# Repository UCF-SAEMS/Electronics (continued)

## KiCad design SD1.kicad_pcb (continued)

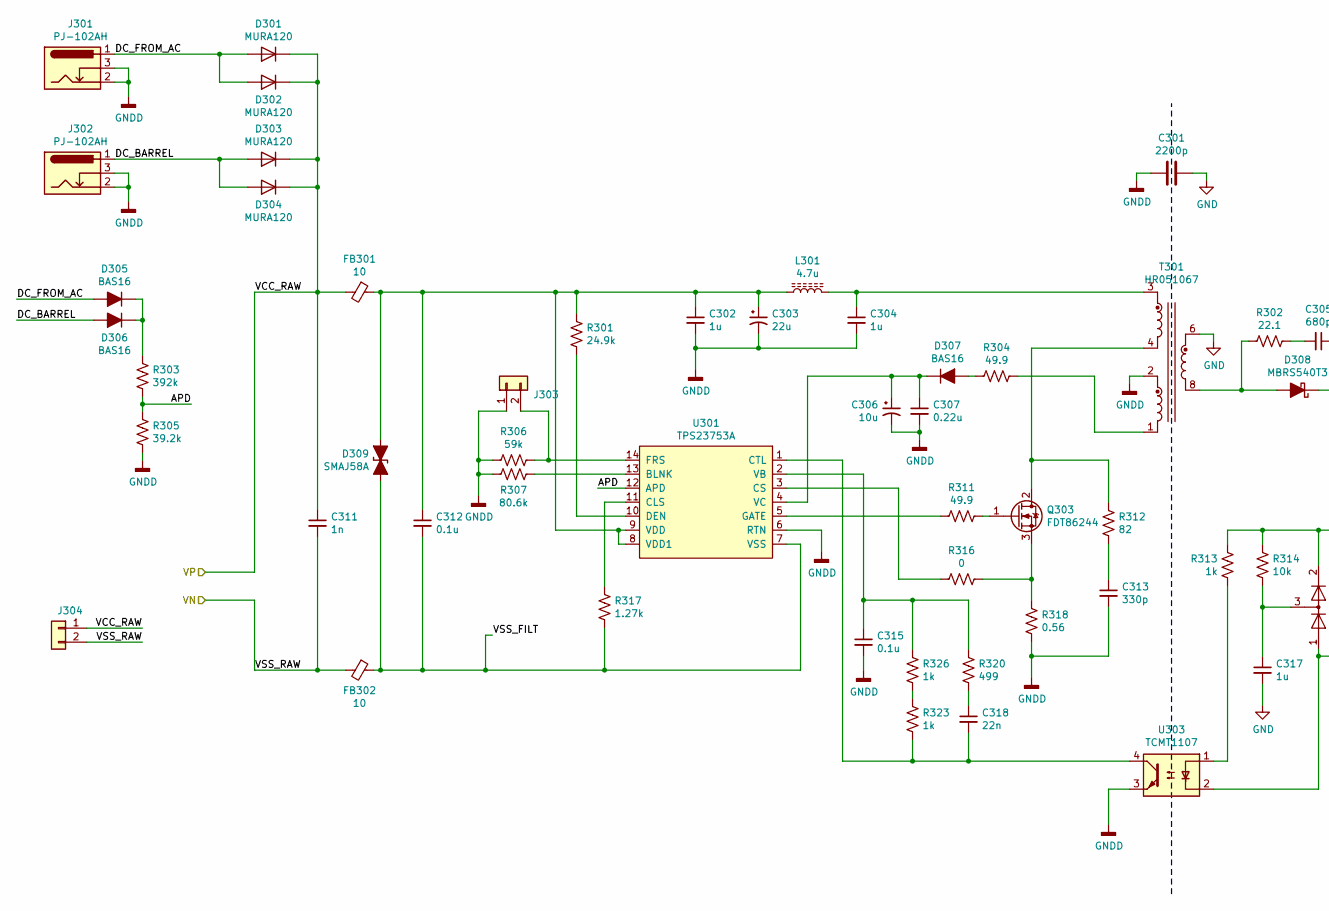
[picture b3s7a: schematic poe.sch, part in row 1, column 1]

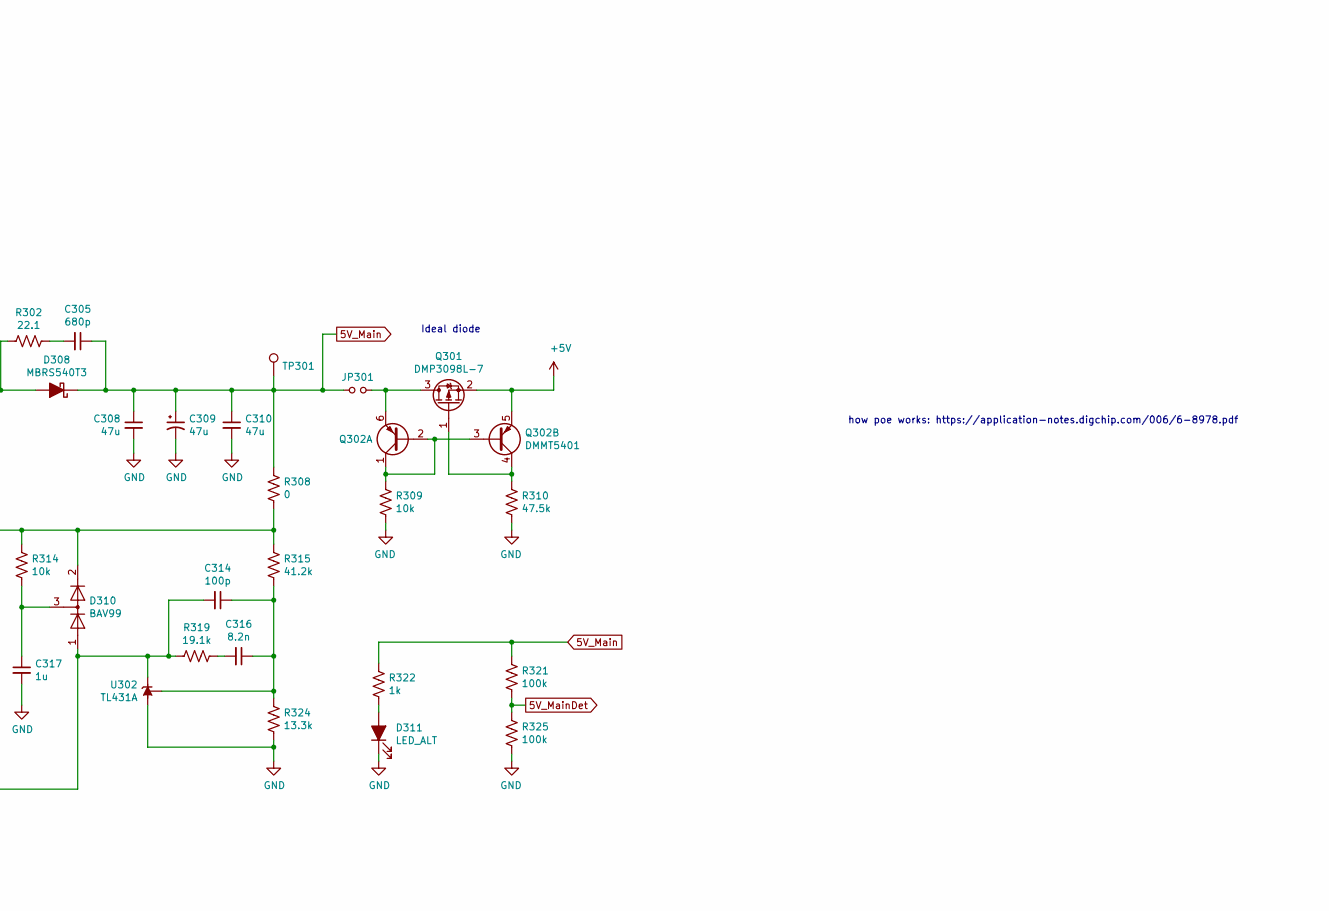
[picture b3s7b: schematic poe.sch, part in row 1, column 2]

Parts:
C301: 2200p; C_1812_4532Metric; Voltage 2kV; MPN 202S43W222KV4E; LCSC C426624
C302, C304: 1u; C_1210_3225Metric; Voltage 100V; MPN C1210C105K1RACAUTO; Digikey 399-7044-1-ND
C303: 22u; C_Elec_6.3x7.7; Voltage 63V; MPN EEHZC1J220XP; Digikey P15467CT-ND
C305: 680p; C_0603_1608Metric; Voltage 25V; MPN 0603B681K500CT; Digikey 1292-1458-1-ND
C306: 10u; CP_Elec_4x5.8; Voltage 16V; MPN EEEHD1C100AR; Digikey PCE4949CT-ND
C307: 0.22u; C_0805_2012Metric; Voltage 25V; MPN CL21B224KBFNNNE; Digikey 1276-1093-1-ND
C308, C310: 47u; C_1210_3225Metric; Voltage 10V; MPN 1210X476K160CT; LCSC C396815
C309: 47u; CP_Elec_4x5.8; Voltage 6.3V; MPN EEEFT1C470AR; Digikey P15090CT-ND
C311: 1n; C_0805_2012Metric; Voltage 100V; MPN CL21B102KCANNNC; Digikey 1276-1169-1-ND
C312: 0.1u; C_0805_2012Metric; Voltage 100V; MPN CL21B104KCFWPNE; Digikey 1276-6733-1-ND
C313: 330p; C_0805_2012Metric; Voltage 200V; MPN CC0805KRX7RABB331; Digikey 311-4334-1-ND
C314: 100p; C_0603_1608Metric; Voltage 50V; MPN CL10C101JC8NNNC; Digikey 1276-1295-1-ND
C315: 0.1u; C_0603_1608Metric; Voltage 50V; MPN 0603B104K500CT; Digikey 1292-1643-1-ND
C316: 8.2n; C_0603_1608Metric; Voltage 50V; MPN CC0603KRX7R9BB822; Digikey 311-1811-1-ND
C317: 1u; C_0603_1608Metric; MPN TMK107B7105KA-T; Digikey 587-2984-1-ND
C318: 22n; C_0603_1608Metric; Voltage 50V; MPN CL10B223KC8WPNC; Digikey 1276-CL10B223KC8WPNCCT-ND
D301, D302, D303, D304: MURA120; D_SMA; MPN MURA120T3G; Digikey MURA120T3GOSCT-ND
D305, D306, D307: BAS16; D_SOT-23_ANK; MPN BAS16-7-F; Digikey BAS16-FDICT-ND
D308: MBRS540T3; D_SMC; MPN MBRS540T3G; LCSC C31849
D309: SMAJ58A; D_SMA; MPN SMAJ58CA-E3/61; Digikey SMAJ58CA-E3/61GICT-ND
D310: BAV99; SOT-23; MPN BAV99,215; Digikey 1727-2914-1-ND
D311: LED_ALT; LED_0603_1608Metric; MPN 150060RS75000; Digikey 732-4978-1-ND
FB301, FB302: 10; L_0603_1608Metric; MPN PBY160808T-110Y-N; LCSC C280672
J301, J302: PJ-102AH; BarrelJack_CUI_PJ-102AH_Horizontal; MPN PJ-102AH; Digikey CP-102AH-ND
J303, J304: Conn_01x02; PinSocket_1x02_P2.54mm_Vertical
JP301: Jumper_NO_Small; SolderJumper-2_P1.3mm_Open_TrianglePad1.0x1.5mm
L301: 4.7u; L_Taiyo-Yuden_MD-4040; MPN SLW4030S4R7MST; Digikey 587-5994-1-ND
Q301: DMP3098L-7; SOT-23-6; MPN DMP3098L-7; Digikey DMP3098LDICT-ND
Q302: DMMT5401; SOT-23-6; MPN DMMT5401-7-F; Digikey DMMT5401-FDICT-ND
Q303: FDT86244; SOT-223-3_TabPin2; MPN FDT86244; LCSC C489347
R301: 24.9k; R_0603_1608Metric; MPN RC0603FR-0724K9L; Digikey 311-24.9KHRCT-ND
R302: 22.1; R_0603_1608Metric; MPN RC0603FR-0722R1L; Digikey 311-22.1HRCT-ND
R303: 392k; R_0603_1608Metric; MPN RC0603FR-07392KL; Digikey 311-392KHRCT-ND
R304, R311: 49.9; R_0603_1608Metric; MPN RC0603FR-0749R9L; Digikey 311-49.9HRCT-ND
R305: 39.2k; R_0603_1608Metric; MPN AC0603FR-0739K2L; Digikey YAG3602CT-ND
R306: 59k; R_0603_1608Metric; MPN RC0603FR-0759KL; Digikey 311-59.0KHRCT-ND
R307: 80.6k; R_0603_1608Metric; MPN RC0603FR-0780K6L; Digikey 311-80.6KHRCT-ND
R308, R316: 0; R_0603_1608Metric
R309, R314: 10k; R_0603_1608Metric; MPN RC0603FR-0710KL; Digikey 311-10.0KHRCT-ND
R310: 47.5k; R_0603_1608Metric; MPN RC0603FR-0747K5L; Digikey 311-47.5KHRCT-ND
R312: 82; R_2010_5025Metric; LCSC C421678, C20464
R313, R322, R323, R326: 1k; R_0603_1608Metric; MPN RC0603FR-071KL; Digikey 311-1.00KHRCT-ND
R315: 41.2k; R_0603_1608Metric; MPN RC0603FR-0741K2L; Digikey 311-41.2KHRCT-ND
R317: 1.27k; R_0603_1608Metric; MPN RC0603FR-071K27L; Digikey 311-1.27KHRCT-ND
R318: 0.56; R_1206_3216Metric; MPN KDV12FR560ET; Digikey 273-KDV12FR560ETCT-ND
R319: 19.1k; R_0603_1608Metric; MPN AC0603FR-0719K1L; Digikey 13-AC0603FR-0719K1LCT-ND
R320: 499; R_0603_1608Metric; MPN AC0603FR-07499RL; Digikey 13-AC0603FR-07499RLCT-ND
R321, R325: 100k; R_0603_1608Metric; MPN RC0603FR-07100KL; Digikey 311-100KHRCT-ND
R324: 13.3k; R_0603_1608Metric; MPN RC0603FR-0713K3L; Digikey 311-13.3KHRCT-ND
T301: HR051067; MPN HR051067; LCSC C93830
TP301: TestPoint; PinSocket_1x01_P2.54mm_Vertical
U301: TPS23753A; TSSOP-14_4.4x5mm_P0.65mm; MPN TPS23753APWR; Digikey 296-39365-1-ND
U302: TL431A; SOT-23; MPN TL431ACDBZR; Digikey 296-17328-1-ND
U303: TCMT1107; SOIC-4_4.55x2.6mm_P1.27mm; MPN TCMT1107; LCSC C81148

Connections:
5V_Main: C305.1, C308.1, C309.1, C310.1, D308.1 (K), JP301.1, R308.2, R321.2, R322.1, TP301.1; also elsewhere on the board
5V_MainDet: R321.1, R325.2; also elsewhere on the board
+5V: Q301.2 (S), Q302.5 (E2); also elsewhere on the board
/Eth + PoE/PoE Flyback/APD: R303.2, R305.1, U301.12 (APD)
/Eth + PoE/PoE Flyback/DC_BARREL: D303.2 (A), D304.2 (A), D306.2 (A), J302.1
/Eth + PoE/PoE Flyback/DC_FROM_AC: D301.2 (A), D302.2 (A), D305.2 (A), J301.1
/Eth + PoE/PoE Flyback/VN: C311.2, FB302.2, J304.2; also elsewhere on the board
/Eth + PoE/PoE Flyback/VP: C311.1, D301.1 (K), D302.1 (K), D303.1 (K), D304.1 (K), FB301.2, J304.1; also elsewhere on the board
/Eth + PoE/PoE Flyback/VSS_FILT: C312.2, D309.2 (A2), FB302.1, R317.2, U301.7 (VSS)
GND: C301.1, C308.2, C309.2, C310.2, C317.2, D311.1 (K), R309.2, R310.1, R324.2, R325.1, T301.5, T301.6, U302.3 (A); also elsewhere on the board
GNDD: C301.2, C302.2, C303.2, C304.2, C306.2, C307.2, C313.2, C315.2, J301.2, J301.3, J302.2, J302.3, J303.1, R305.2, R306.2, R307.2, R318.2, T301.2, U301.6 (RTN), U303.3
unnamed: C302.1, C303.1, C312.1, D309.1 (A1), FB301.1, L301.1, R301.1, U301.8 (VDD1), U301.9 (VDD)
unnamed: C304.1, L301.2, T301.3
unnamed: C305.2, R302.1
unnamed: C306.1, C307.1, D307.1 (K), U301.4 (VC)
unnamed: C313.1, R312.2
unnamed: C314.1, C316.1, R315.1, R324.1, U302.2 (REF)
unnamed: C314.2, D310.1 (K), R319.2, U302.1 (K), U303.2
unnamed: C315.1, R320.1, R326.1, U301.2 (VB)
unnamed: C316.2, R319.1
unnamed: C317.1, D310.3 (K), R314.2
unnamed: C318.1, R320.2
unnamed: C318.2, R323.2, U301.1 (CTL), U303.4
unnamed: D305.1 (K), D306.1 (K), R303.1
unnamed: D307.2 (A), R304.2
unnamed: D308.2 (A), R302.2, T301.7, T301.8
unnamed: D310.2 (A), R308.1, R313.1, R314.1, R315.2
unnamed: D311.2 (A), R322.2
unnamed: J303.2, R306.1, U301.14 (FRS)
unnamed: JP301.2, Q301.3 (D), Q302.6 (E1)
unnamed: Q301.1 (G), Q302.4 (C2), R310.2
unnamed: Q302.1 (C1), Q302.2 (B1), Q302.3 (B2), R309.1
unnamed: Q303.1 (G), R311.1
unnamed: Q303.2 (D), R312.1, T301.4
unnamed: Q303.3 (S), R316.1, R318.1
unnamed: R301.2, U301.10 (DEN)
unnamed: R304.1, T301.1
unnamed: R307.1, U301.13 (BLNK)
unnamed: R311.2, U301.5 (GATE~)
unnamed: R313.2, U303.1
unnamed: R316.2, U301.3 (CS)
unnamed: R317.1, U301.11 (CLS)
unnamed: R323.1, R326.2

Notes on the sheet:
how poe works: https://application-notes.digchip.com/006/6-8978.pdf
Ideal diode

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
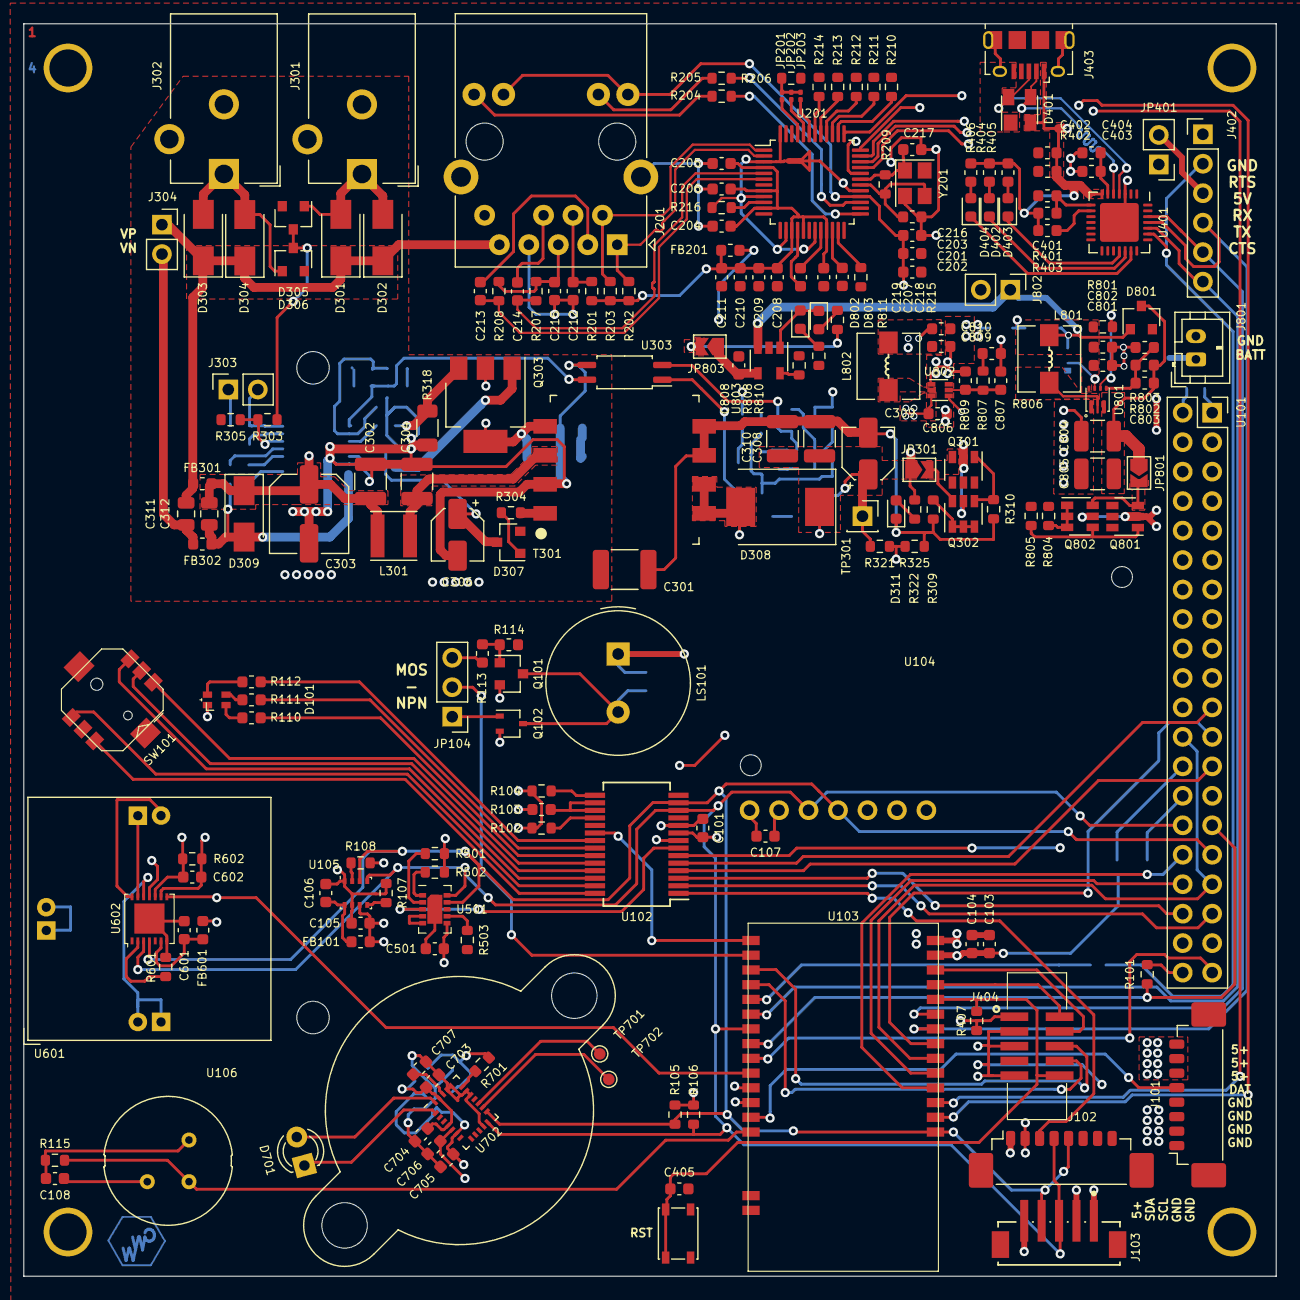
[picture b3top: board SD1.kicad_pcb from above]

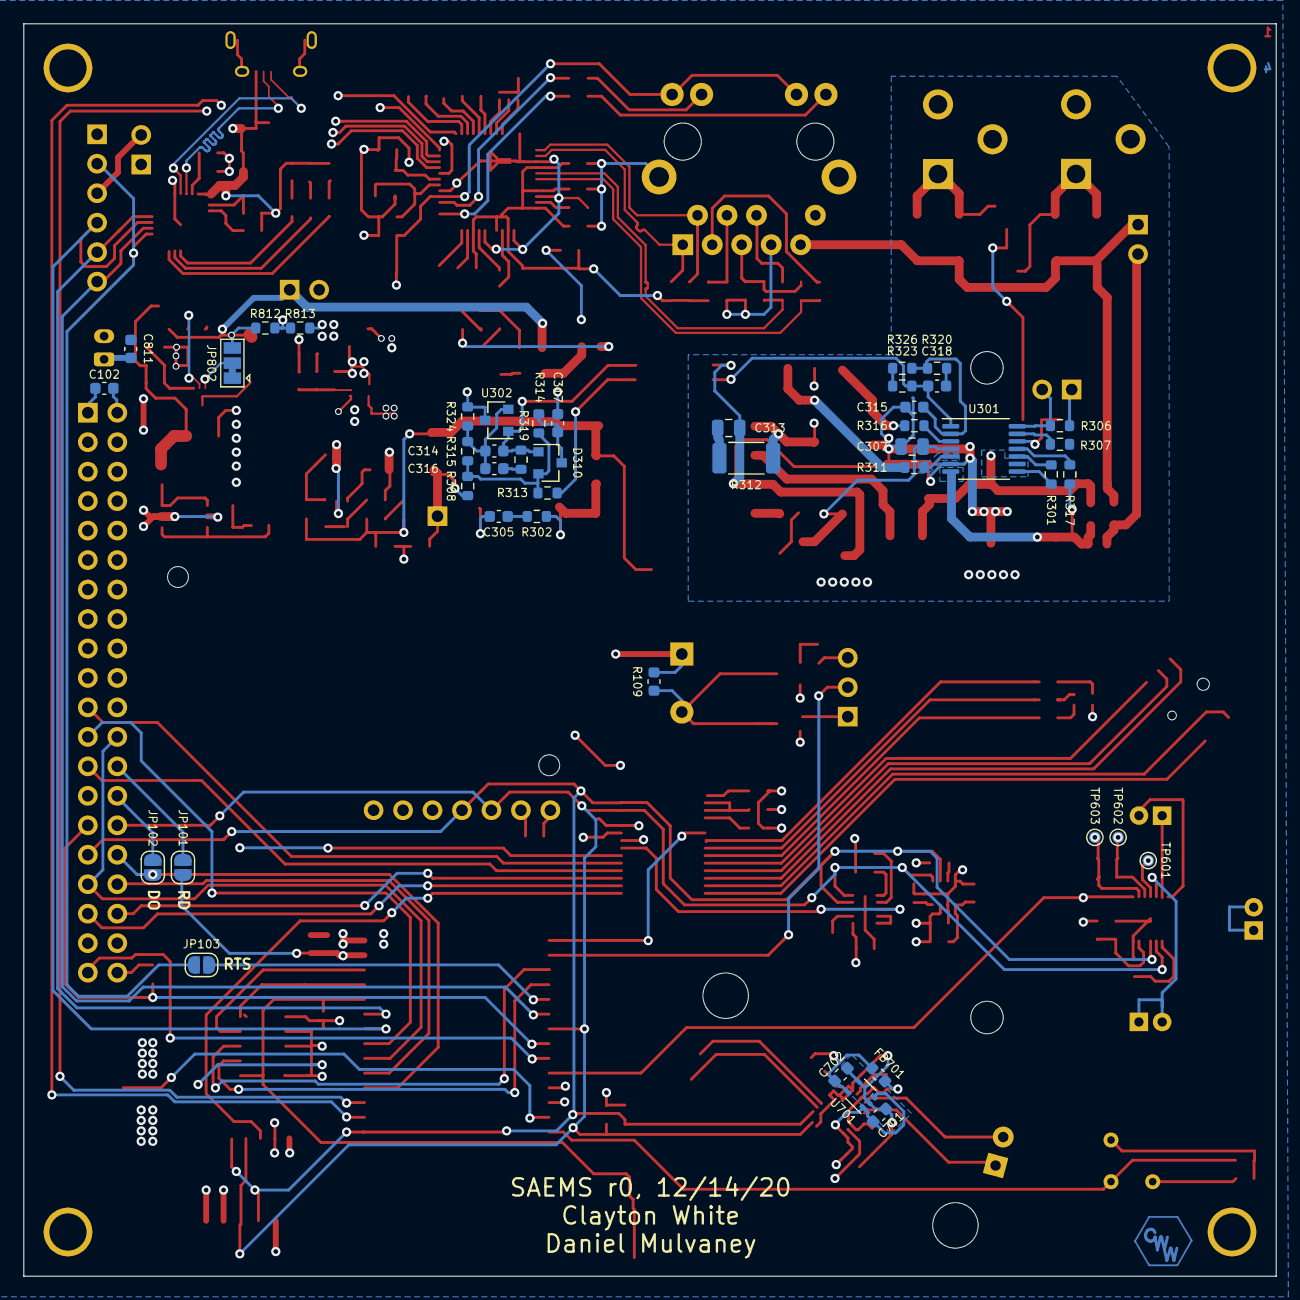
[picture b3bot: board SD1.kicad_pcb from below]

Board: 4 copper layers, 108.0 x 108.0 mm, 252 parts (45 on the bottom side), 179 nets.

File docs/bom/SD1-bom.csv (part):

Row,Description,Part,References,Value,Footprint,Quantity Per PCB,Datasheet,Manufacturer,MPN,Note,Digikey,DNP,LCSC,Mouser,Error,Mfr,Size,Type,Voltage,Current,Power,Volt,Alt
1,Particulate Matter Sensor I²C,SPS30,$U101,SPS30,,1,,,SPS30,PM2.5 PARTICLE SENSOR,1649-1106-ND,,,,,,,,,,,,
2,"Unpolarized capacitor, small symbol",C_Small,C602,0,C_0603_1608Metric,1,~,,,,,1,,,,,,,,,,,
3,"Unpolarized capacitor, small symbol",C_Small,C216 C217,20p,C_0603_1608Metric,2,~,,CC0603JRNPO9BN200,CAP CER 20PF 50V C0G/NPO 0603,311-1424-1-ND,,C105621,,,,,,,,,,
4,"Unpolarized capacitor, small symbol",C_Small,C314 C803 C807,100p,C_0603_1608Metric,3,~,,CL10C101JC8NNNC,CAP CER 100PF C0G 50V 0603,1276-1295-1-ND,1,C296717,,5%,,0603,C0G,50V,,,,
5,"Unpolarized capacitor, small symbol",C_Small,C313,330p,C_0805_2012Metric,1,~,,CC0805KRX7RABB331,CAP CER 330PF X7R 200V 0805,311-4334-1-ND,,C527231,,10%,,0805,X7R,200V,,,,
6,"Unpolarized capacitor, small symbol",C_Small,C305,680p,C_0603_1608Metric,1,~,,0603B681K500CT,CAP CER 680PF 25V X7R 0603,1292-1458-1-ND,,C335547,,10%,,0603,X7R,25V,,,,
7,"Unpolarized capacitor, small symbol",C_Small,C311,1n,C_0805_2012Metric,1,~,,CL21B102KCANNNC,CAP CER 1NF X7R 100V 0805,1276-1169-1-ND,,C15177,,10%,,0805,X7R,100V,,,,
8,Unpolarized capacitor,C,C301,2200p,C_1812_4532Metric,1,~,,202S43W222KV4E,CAP CER 2.2NF 2kV X7R 1812,,,C426624,,10%,,1812,X7R,2kV,,,,
9,"Unpolarized capacitor, small symbol",C_Small,C213 C214,6.8n,C_0603_1608Metric,2,~,,CC0603KRX7R9BB682,CAP CER 6800PF 50V X7R 0603,311-1084-1-ND,,C107097,,,,,,,,,,
10,"Unpolarized capacitor, small symbol",C_Small,C215 C316,8.2n,C_0603_1608Metric,2,,,CC0603KRX7R9BB822,CAP CER 8.2NF X7R 50V 0603,311-1811-1-ND,,C113812,,10%,,0603,X7R,50V,,,,
11,"Unpolarized capacitor, small symbol",C_Small,C212 C318,22n,C_0603_1608Metric,2,~,,CL10B223KC8WPNC,CAP CER 22NF X7R 50V 0603,1276-CL10B223KC8WPNCCT-ND,,C472763,,10%,,0603,X7R,50V,,,,
12,"Unpolarized capacitor, small symbol",C_Small,C105 C106 C108 C203 C204 C205 C206 C207 C208 C209 C218 C315 C401 C403 C405 C501 C601 C703 C704,0.1u,C_0603_1608Metric,19,~,,0603B104K500CT,CAP CER 0.1UF 50V X7R 0603,1292-1643-1-ND,,,,10%,,0603,X7R,50V,,,,
13,"Unpolarized capacitor, small symbol",C_Small,C312,0.1u,C_0805_2012Metric,1,~,,CL21B104KCFWPNE,CAP CER 0.1UF X7R 100V 0805,1276-6733-1-ND,,C307361,,10%,,0805,X7R,100V,,,,
14,"Unpolarized capacitor, small symbol",C_Small,C307,0.22u,C_0805_2012Metric,1,~,,CL21B224KBFNNNE,CAP CER 220NF 25V X7R 0805,1276-1093-1-ND,,C5378,,10%,,0805,X7R,25V,,,,
15,"Unpolarized capacitor, small symbol",C_Small,C102 C104 C317 C701 C702 C707,1u,C_0603_1608Metric,6,~,,TMK107B7105KA-T,CAP CER 1UF 25V X7R 0603,587-2984-1-ND,,,,,,,,,,,,
16,"Unpolarized capacitor, small symbol",C_Small,C302 C304,1u,C_1210_3225Metric,2,~,,C1210C105K1RACAUTO,CAP CER 1UF 100V X7R 1210,399-7044-1-ND,,C129676,,10%,,1210,X7R,100V,,,,
17,"Unpolarized capacitor, small symbol",C_Small,C201 C202 C210 C211 C219 C402 C404 C808 C811,4.7u,C_0603_1608Metric,9,~,,C0603C475K9PACTU,CAP CER 4.7UF 6.3V X5R 0603,399-3482-1-ND,,C86016,,,,,,,,,,
18,"Unpolarized capacitor, small symbol",C_Small,C101 C103 C107 C705 C706 C801 C802 C806 C809 C810,10u,C_0603_1608Metric,10,,,C1608X5R1A106M080AC,CAP CER 10UF 10V X5R 0603,445-6853-1-ND,,,,,,,,,,,,
19,"Polarized capacitor, small US symbol",CP1_Small,C306,10u,CP_Elec_4x5.8,1,~,,EEEHD1C100AR,CAP ALU 10UF 16V 4x5.8,PCE4949CT-ND,,C401842,,20%,,.2x.21in,Aluminum,16V,,,,
20,"Polarized capacitor, small US symbol",CP1_Small,C303,22u,C_Elec_6.3x7.7,1,~,,EEHZC1J220XP,CAP ALU 22UF 63V 6.3x7.7,P15467CT-ND,,C264048,,20%,,.26x.276in,Aluminum,63V,,,,
21,"Unpolarized capacitor, small symbol",C_Small,C308 C310 C804 C805,47u,C_1210_3225Metric,4,,,1210X476K160CT,CAP CER 47UF X5R 10V 1210,587-5922-1-ND,,C396815,,20%,,1210,X5R,10V,,,,
22,"Polarized capacitor, small US symbol",CP1_Small,C309,47u,CP_Elec_4x5.8,1,~,,EEEFT1C470AR,CAP ALU 47UF  6.3V 4x5.8,P15090CT-ND,,C178589,,20%,,.2x.21in,Aluminum,6.3V,,,,
23,"Diode, filled shape",D_ALT,D305 D306 D307 D801,BAS16,D_SOT-23_ANK,4,~,,BAS16-7-F,DIODE GEN PURP 75V 200MA SOT23-3,BAS16-FDICT-ND,,C69162*,,,,,,,150mA,350mW,75V,
24,"BAV99 High-speed switching diodes, SOT-23",BAV99,D310,BAV99,SOT-23,1,https://assets.nexperia.com/documents/data-sheet/BAV99_SER.pdf,,"BAV99,215","BAV99 switching diode, generic",1727-2914-1-ND,,C152481,,,,,,,,,,
25,"Light emitting diode, filled shape",LED_ALT,D311 D402 D403 D404 D802 D803,LED_ALT,LED_0603_1608Metric,6,,,150060RS75000,LED RED CLEAR 0603 SMD,732-4978-1-ND,,C205443,,,,,,,,,,
26,"RGB LED, red/green/blue/anode",LED_RGBA,D101,LED_RGBA,LED_19-237_1.6x1.6mm,1,~,,19-237,RGB PCB TOP VIEW SMD LED 0606,19-237A/R6GHBHC-B01/2T,,C264508,,,,,,,,,,
27,"Schottky diode, filled shape",D_Schottky_ALT,D308,MBRS540T3,D_SMC,1,~,,MBRS540T3G,"RECTIFIER DIODE, SCHOTTKY, 5A, 4",,,C31849,,,,,,,5A,,40V,
28,Diode,D,D301 D302 D303 D304,MURA120,D_SMA,4,~,,MURA120T3G,,MURA120T3GOSCT-ND,,C111832,,,,,,,1A,,200V,
29,"Photodiode, filled shape",D_Photo_ALT,D701,Photodiode alt,LED_D3.0mm_Clear,1,~,,PD204-6C,SENSOR PHOTODIODE 940NM RADIAL,1080-1140-ND,,C264281,,,,,,,,,,
30,"Bidirectional transient-voltage-suppression diode, filled shape",D_TVS_ALT,D309,SMAJ58A,D_SMA,1,~,,SMAJ58CA-E3/61,TVS DIODE 58V 93.6V DO214AC,SMAJ58CA-E3/61GICT-ND,,C506567,,,,,,,,1W,58V,
31,"TVS Diode Array, 5.5V Standoff, 3 Channels, SOT-143 package",SP0503BAHT,D401,SP0503BAHT,SOT-143,1,http://www.littelfuse.com/~/media/files/littelfuse/technical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,,SP0503BAHTG,TVS DIODE 5.5V 8.5V SOT143-4,F2715CT-ND,,C7074,,,,,,,,,,
32,"Ferrite bead, small symbol",Ferrite_Bead_Small,FB301 FB302,10,L_0603_1608Metric,2,~,Chilisin Elec,PBY160808T-110Y-N,11Ω @ 100MHz 4A 1 20mΩ 0603 Ferrite Beads,,,C280672,,,MMZ2012R150AT000,,,,,,,
33,"Ferrite bead, small symbol",Ferrite_Bead_Small,FB101 FB201 FB601 FB701,Ferrite_Bead_Small,L_0603_1608Metric,4,~,,BLM18PG471SN1D,470 Ohms @ 100MHz 1 Power Line Ferrite Bead 0603 1A 200mOhm,490-5223-1-ND,,C97853,81-BLM18PG471SN1D,,,,,,,,,
34,USB Micro Type B connector,USB_B_Micro,J403,10118194-0001LF,USB_Micro-B_Amphenol_10118194_Horizontal,1,~,,10118194-0001LF,CONN RCPT USB2.0 MICRO B SMD R/A,609-4618-1-ND,,C132563,,,,,,,,,,
35,"Generic connector, single row, 01x02, script generated (kicad-library-utils/schlib/autogen/connector/)",Conn_01x02,J303 J304,Conn_01x02,PinSocket_1x02_P2.54mm_Vertical,2,~,,,,,,,,,,,,,,,,
36,"Generic connector, single row, 01x02, script generated (kicad-library-utils/schlib/autogen/connector/)",Conn_01x02,J801,Conn_01x02,JST_PH_B2B-PH-K_1x02_P2.00mm_Vertical,1,~,,B2B-PH-K-S(LF)(SN),CONN HEADER VERT 2POS 2MM,B2B-PH-K-S(LF)(SN),,C131337,,,,,,,,,,
37,"Generic connector, single row, 01x02, script generated (kicad-library-utils/schlib/autogen/connector/)",Conn_01x02,J802,Conn_01x02,PinHeader_1x02_P2.54mm_Vertical,1,~,,,,,,,,,,,,,,,,
38,"Generic connector, single row, 01x11, script generated (kicad-library-utils/schlib/autogen/connector/)",Conn_01x11,J401,Conn_01x11,Molex_SL_171971-0011_1x11_P2.54mm_Vertical,1,~,,,TI Eval connector,,,,,,,,,,,,,
39,"Cortex Debug Connector, standard ARM Cortex-M SWD and JTAG interface",Conn_ARM_JTAG_SWD_10,J404,Conn_ARM_JTAG_SWD_10,PinHeader_2x05_P1.27mm_Wide_Shrouded_Vertical_SMD,1,http://infocenter.arm.com/help/topic/com.arm.doc.ddi0314h/DD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,,FTSH-105-01-L-DV-K,2x5 1.27mm SMD connector,SAM8799-ND,,,,,,,,,,,,BXIDM03
40,"FTDI, USB to serial TTL cable",FTDI_TTL_Cable,J402,FTDI_TTL_Cable,PinHeader_1x06_P2.54mm_Vertical,1,,,,,,,C190819,,,,,,,,,,
41,RJ45 PoE 10/100 Base-TX Jack with Magnetic Module,RJ45_Abracon_ARJP11A-MASA-B-A-EMU2,J201,HR861153C,RJ45_Abracon_ARJP11A-MA_Horizontal,1,https://abracon.com/Magnetics/lan/ARJP11A.PDF,,ARJP11A-MASA-B-A-EMU2,Alt HR861153C verified,ARJP11A-MASA-B-A-EMU2-ND,,HR861153C,,,,,,,,,,
42,"Generic connectable mounting pin connector, single row, 01x08, script generated (kicad-library-utils/schlib/autogen/connector/)",Conn_01x08_MountingPin,J101,JST 1.25mm,Molex_PicoBlade_53398-0871_1x08-1MP_P1.25mm_Vertical,1,~,,0533980871,,WM7612CT-ND,,C53040,,,,,,,,,,
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
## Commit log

2020-10-21 Initial kicad dump
    With usb-serial, poe, display, and micro
2020-10-21 Adding LED driver
    Initial commit CREE LED driver
2020-10-26 Boilerplate for CO sensor
2020-10-26 Add VOC sensor
2020-10-28 Added CO sensor
    Carbon Monoxide Sensor layout
2020-10-28 Minor cleanup
2020-10-28 Led horiz
2020-10-29 Finish up led
2020-10-31 Add PIR motion and sheet for smoke
2020-11-05 Added Smoke Sensor
2020-11-05 Minor smoke cleanup
2020-11-06 Add SPS30 PMS sensor
    -Fix cap
2020-11-06 Add BME280
2020-11-06 Minor part picking and annotation
2020-11-06 Add SCD30 co2 sensor
2020-11-08 Major power changes
    Added 5v boost, 3.3 buck, ideal diode circuits.
    Poe: added barrel jacks
    Smoke: general cleanup
2020-11-08 Starting pin assignment
2020-11-08 Continue part picking
2020-11-13 Set transformer footprint
2020-11-13 PoE layout
    Changed opto and fixed ref diode footprint/symbol
2020-11-15 Layout for Smoke and Reference Indicators for PoE
2020-11-18 Modified layout for Smoke, Fixed Ideal Diode
2020-11-20 Add smoke chamber to sch and layout
2020-11-21 Add pull down for display backlight
    When h-z the backlight partially turns on. Possible to DAC this instead of PWM. Appears to use a NPN instead of a NMOS.
2020-11-21 Added battery charger schematic
    Annotated
2020-11-21 5V boost and 3.3V buck layout
2020-11-21 Cleaned up, Annotated
    Added Global 5V_Main net, solder jumper for battery charger, jumper for speaker and speaker_alt, added parts for battery charger
2020-11-22 Add resistor to battery indicator, battery layout, update font sizes
2020-11-22 Add JST cable for easier integration
    Carries power, data and ground over a JST 1.25mm
2020-11-22 Added RGBW connector
2020-11-28 Add diodes to seperate APD
    Previously the APD feedback network directly shorted DC_FROM_AC and DC_BARREL together.
2020-11-29 4layer layout WIP
2020-11-29 Bugfix: critical net name error for target VDD and debugging connectors
2020-11-29 Bugfix: net name error for LCD reset
2020-12-01 4layer layout WIP, 90%.
    Changed SCD30 to reverse mount.
    Connected RGB led and button to io expander.
    Connected all nets to micro.
    Add jumper for CTS line.
    Nettie GNDA and GND for W5500 Eth.
    Changed EN_5V_BST to Global.
2020-12-11 Layout WIP, sch final
    USB 5V Jumper works for both FTDI and microusb
    Added decoupling caps for micro
2020-12-11 Re-annotate all parts
    Cleans up annotations
2020-12-11 Prefinal, layout done
    Update FB to use inductor footprints
    DNP net tie
    Update diode symbol in power
    Add battery voltage divider in power
    Supply 5V power to aux sensor connector
2020-12-12 BOM reduction and part picking
2020-12-12 Trace length matching for ETH and USB
2020-12-12 BOM update and text cleanup
2020-12-16 Prep for gerber export
    Update fields
    Align standoff holes
2020-12-16 Increase clearance for SWD connector
    Alternatives are:
    FTSH-105-01-L-DV-K
    BXIDM03
    3221-10-0300-00
2021-01-11 Soldermask clearance fix
2021-01-18 Schematic field cleanup
    Remove stray spaces
    Cleaned up duplicate fields
    Normalize: 100pF (C314 C803 C807) and 47uF (C308 C310 C804 C805) according to r0 order
2021-01-18 Add generated files
    Added title block to pcb
    Fixed backup lib for USB connector
2021-01-18 Schematic field cleanup
    Fixed rescue libs
    Remove stray spaces
2021-01-18 Add generated files
2021-01-22 Added SAEMS_LedDriver.png (draw.io)
2021-01-22 Add flowchart to readme
2021-02-25 Added SAEMS_MainboardBlock.png (draw.io) block diagram
2021-02-25 Update README.md
    Fix draw.io edit link
2021-03-14 Initial flash mod
    Add on module for additional flash memory
2021-03-14 Flash mod add generated files
